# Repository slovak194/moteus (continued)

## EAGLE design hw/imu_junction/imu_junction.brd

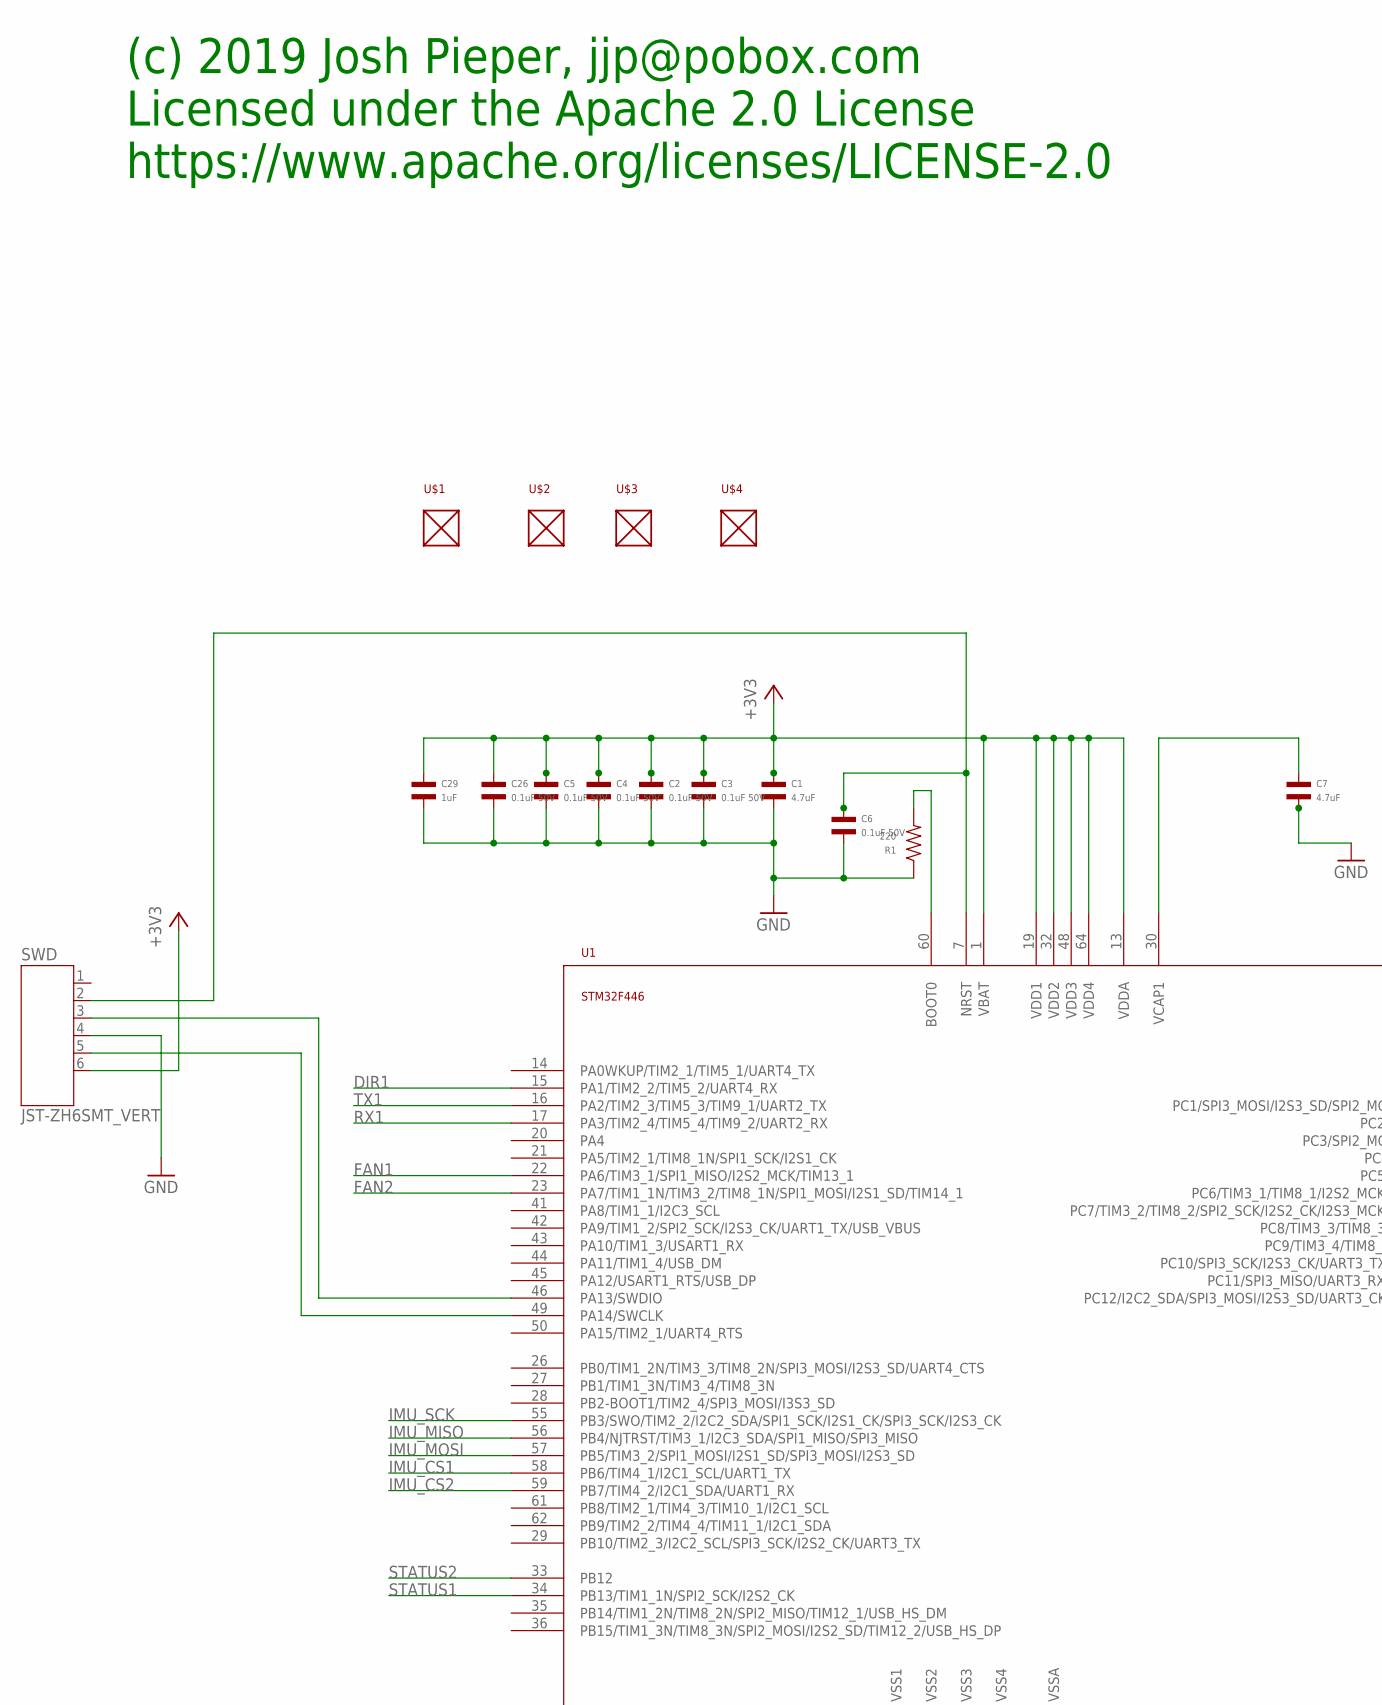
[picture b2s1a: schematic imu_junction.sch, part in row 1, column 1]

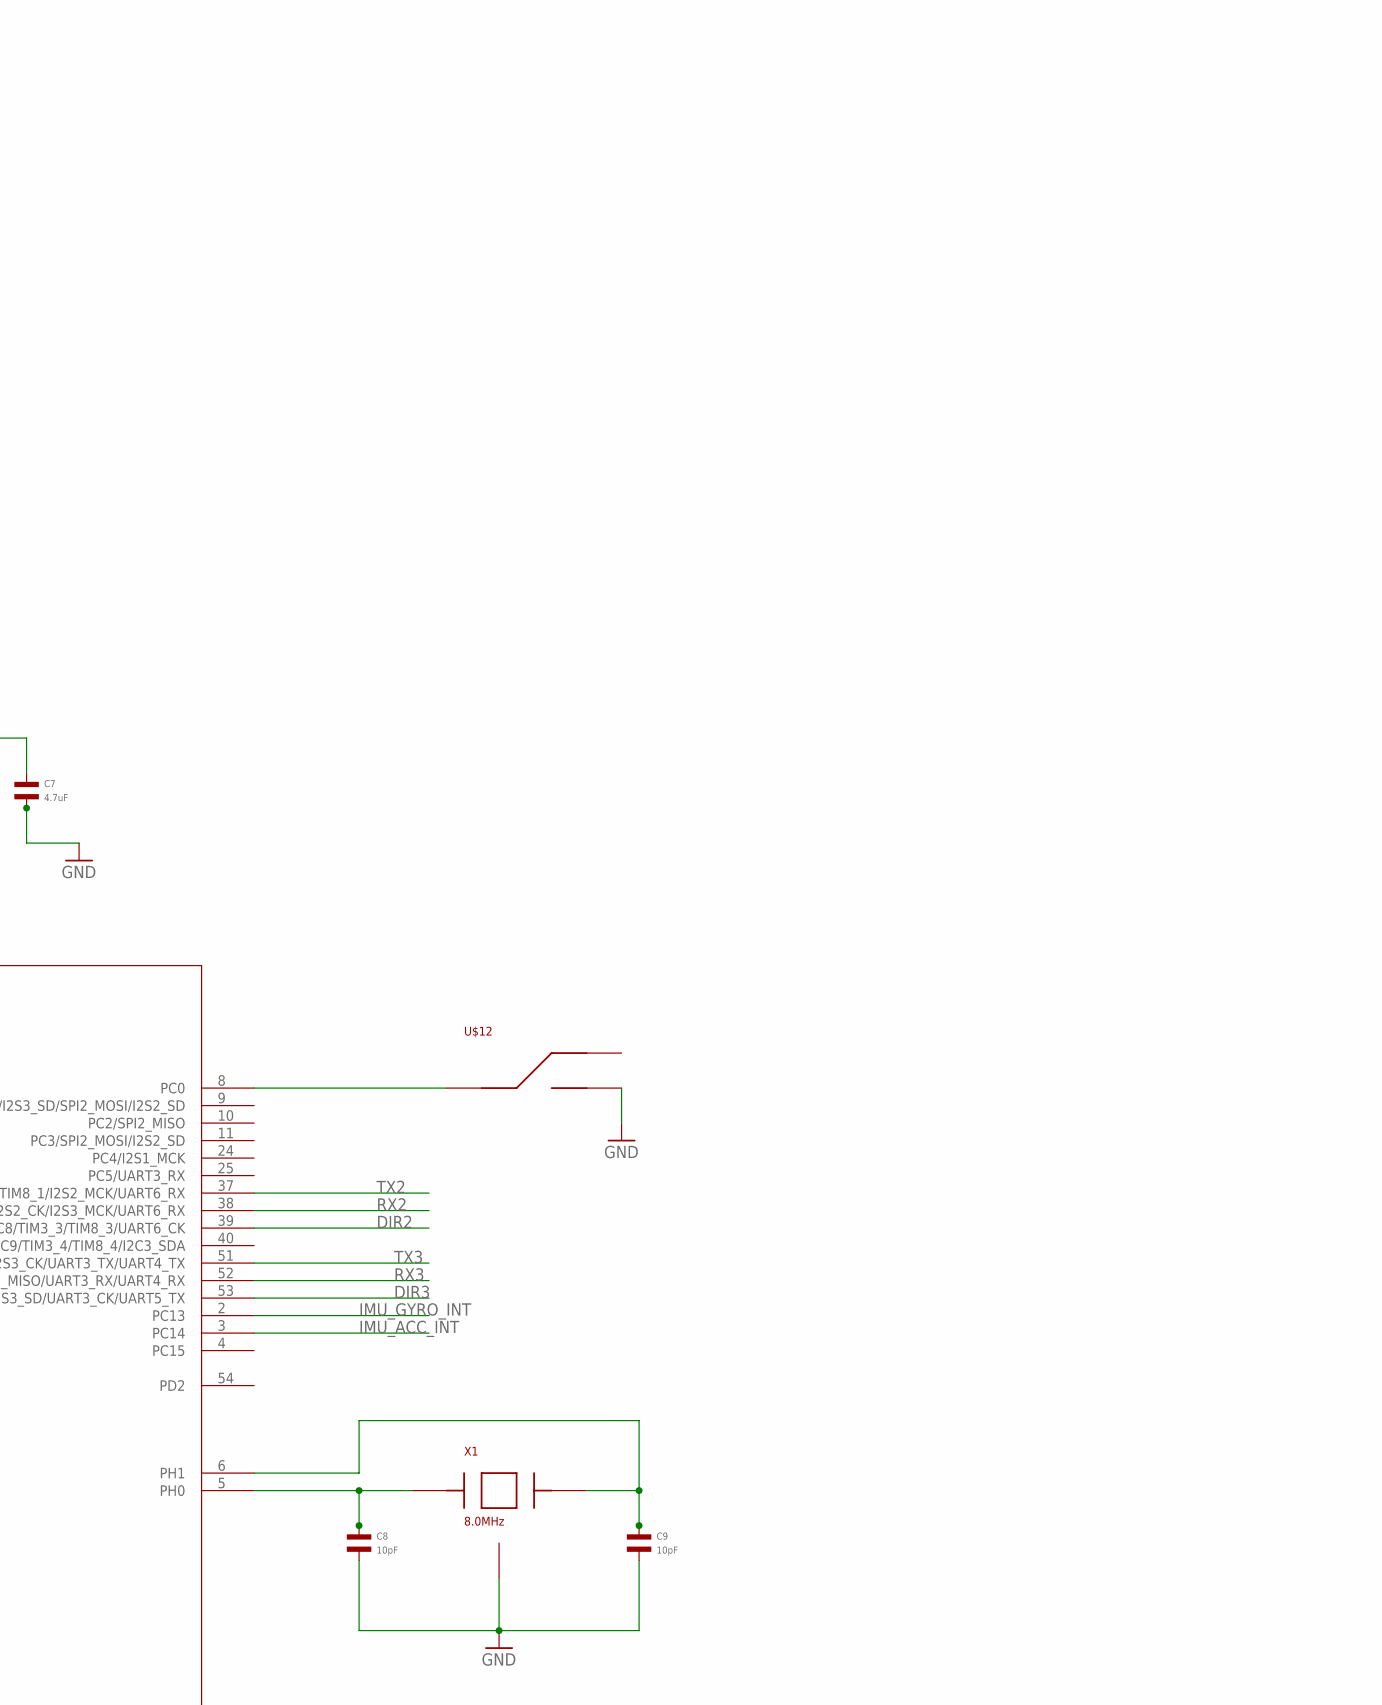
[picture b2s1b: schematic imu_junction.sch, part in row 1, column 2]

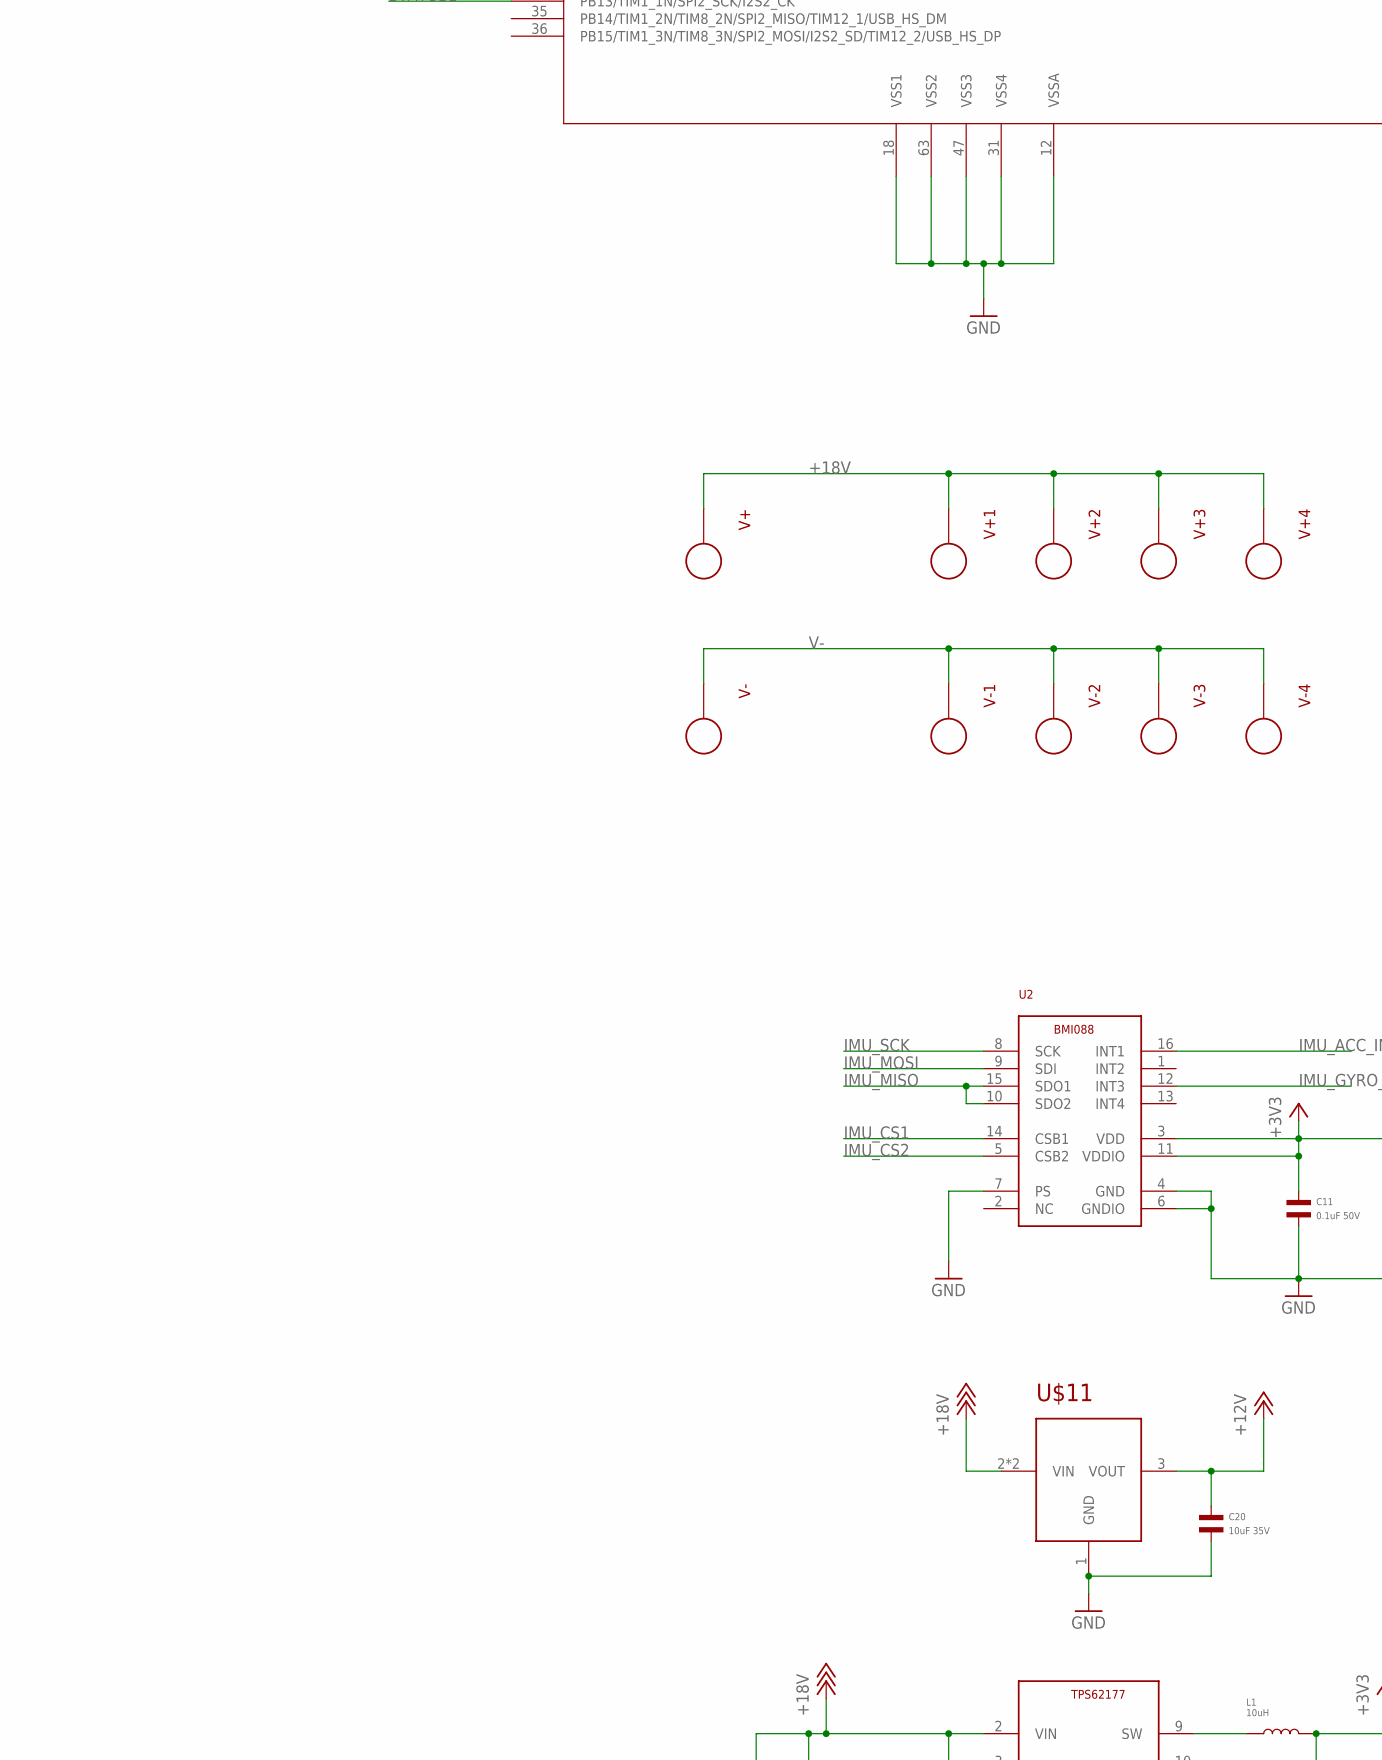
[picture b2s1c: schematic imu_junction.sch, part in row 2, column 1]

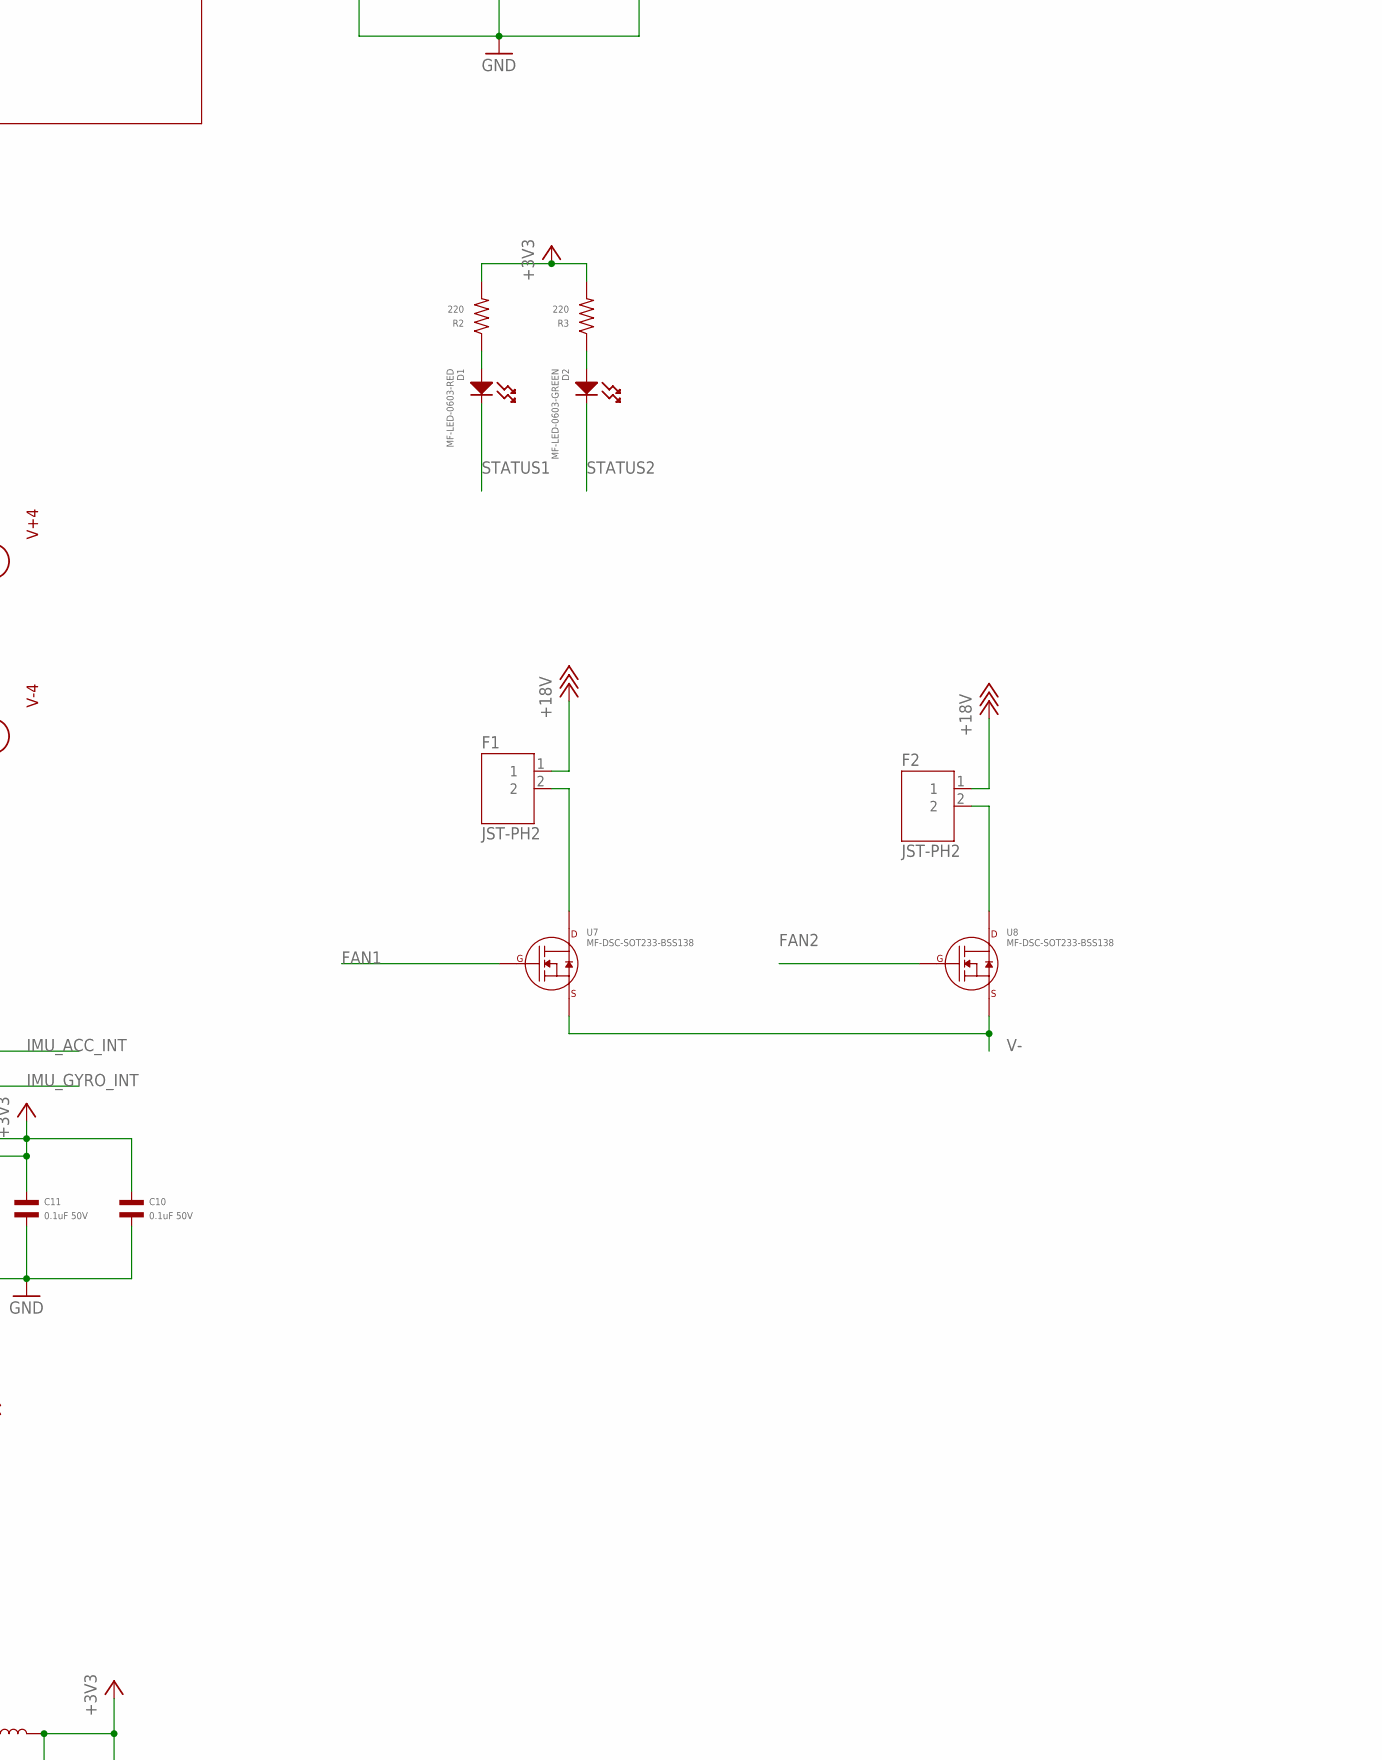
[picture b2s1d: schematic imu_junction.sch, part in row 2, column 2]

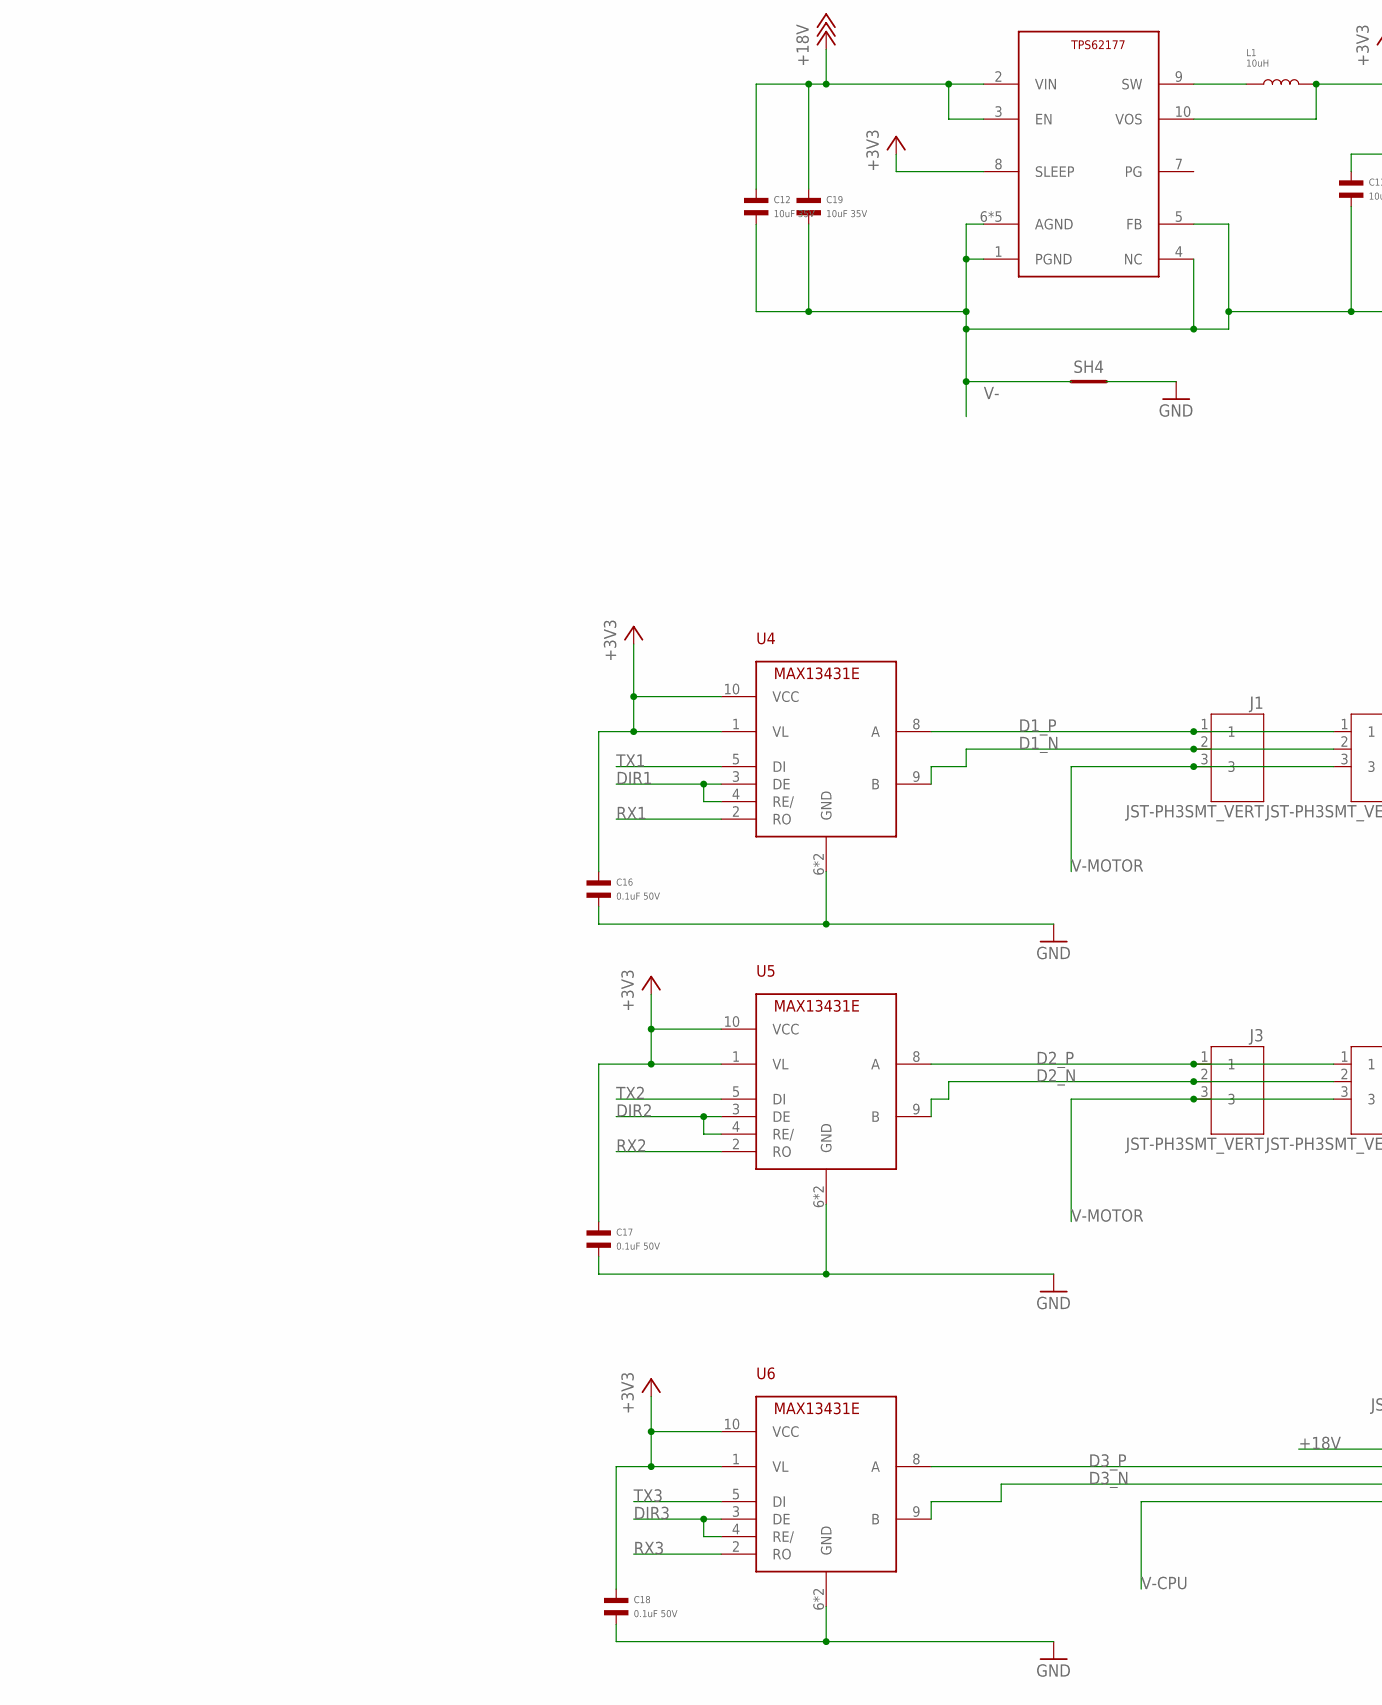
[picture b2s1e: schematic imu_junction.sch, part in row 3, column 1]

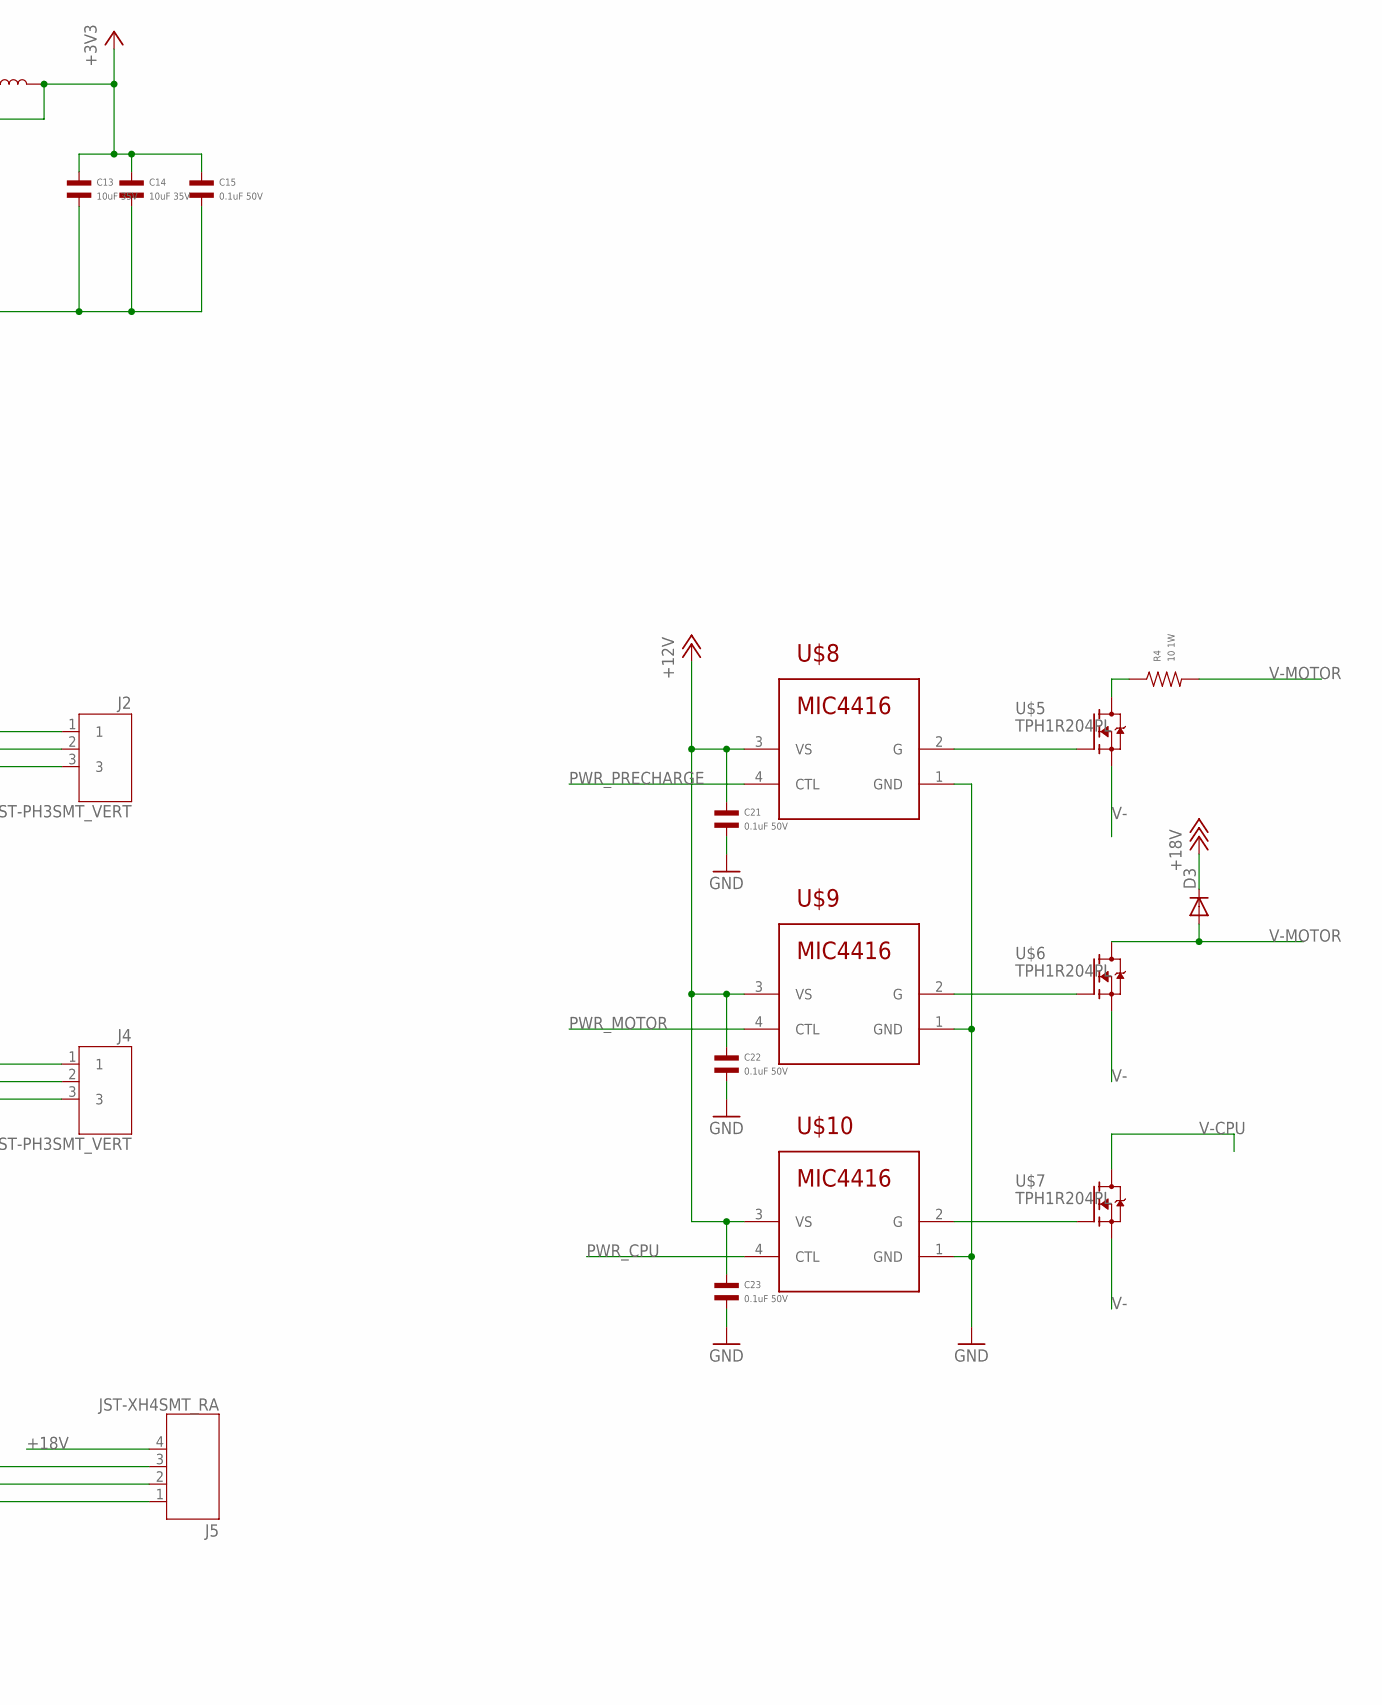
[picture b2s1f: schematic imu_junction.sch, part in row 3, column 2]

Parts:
C1, C7: 4.7uF; C0603; MPN CL10A475KA8NQNC
C2, C3, C4, C5, C6, C10, C11, C15, C16, C17, C18, C21, C22, C23, C26: 0.1uF 50V; C0402; MPN 0402B104K500CT
C8, C9: 10pF; C0603; MPN MF-CAP-0603-10pF
C12, C13, C14, C19, C20: 10uF 35V; C1206; MPN CGA5L1X7R1V106K160AC
C29: 1uF; C0402; MPN MF-CAP-0402-1uF
D1: MF-LED-0603-RED; LED0603
D2: MF-LED-0603-GREEN; LED0603
D3: DIODE-; DO-214AB
F1, F2: JST-PH2; JST_S2B-PH-SM4-TB(LF)(SN); MPN B2B-PH-SM4-TB(LF)(SN)
J1, J2, J3, J4: JST-PH3SMT_VERT; JST_B3B_PH-SM4-TB(LF)(SN); MPN B3B-PH-SM4-TB(LF)(SN)
J5: JST-XH4SMT_RA; JST_XH_SMT_RA_4; MPN S4B-XH-SM4-TB(LF)(SN)
L1: 10uH; L1210; MPN MF-IND-1210-10uH
R1, R2, R3: 220; R0402; MPN MF-RES-0402-220
R4: 10 1W; R1206; MPN HRG3216Q-10R0-D-T1
SH4: SHORTBIG; SHORT_TOP-BIG
SWD: JST-ZH6SMT_VERT; JST_B6B-ZR-SM4-TF(LF)(SN); MPN B6B-ZR-SM4-TF(LF)(SN)
U1: STM32F4R_64PIN; LQFP64; MPN STM32F446RET6
U2: BMI088LGA16; LGA16; MPN BMI088
U3: TPS62177WSON10; WSON10; MPN TPS62177DQCR
U4, U5, U6: MAX13431E; TDFN10; MPN MAX13431EETB+T
U7, U8: MF-DSC-SOT233-BSS138; SOT-23-3
U$1, U$2, U$3, U$4: MOUNTM2; M2MOUNT
U$5, U$6, U$7: TPH1R204PL; SOP_ADVANCE
U$8, U$9, U$10: MIC4416; SOT143
U$11: ZXTR2012Z; SOT89
U$12: SLIDE_SWITCHJS_SUB_SWITCH; JS_SUB_SWITCH
V+, V+1, V+2, V+3, V+4: PAD12AWG_PAD; 12AWG_PAD
V-, V-1, V-2, V-3, V-4: PAD12AWG_PAD; 12AWG_PAD
X1: 8.0MHz; ABM3B; MPN ABM3B-8.000MHZ-10-1-U-T

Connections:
+3V3: C1.P$1, C2.P$1, C3.P$1, C4.P$1, C5.P$1, C10.P$1, C11.P$1, C13.P$1, C14.P$1, C15.P$1, C16.P$1, C17.P$1, C18.P$1, C26.P$1, C29.P$1, L1.P$2, R2.P$2, R3.P$2, SWD.6, U1.1 (VBAT), U1.13 (VDDA), U1.19 (VDD1), U1.32 (VDD2), U1.48 (VDD3), U1.64 (VDD4), U2.3 (VDD), U2.11 (VDDIO), U3.8 (SLEEP), U3.10 (VOS), U4.1 (VL), U4.10 (VCC), U5.1 (VL), U5.10 (VCC), U6.1 (VL), U6.10 (VCC)
+12V: C20.P$1, C21.P$1, C22.P$1, C23.P$1, U$8.3 (VS), U$9.3 (VS), U$10.3 (VS), U$11.3 (VOUT)
+18V: C12.P$1, C19.P$1, D3.C, F1.1, F2.1, J5.4, U3.2 (VIN), U3.3 (EN), U$11.2 (VIN), U$11.PAD (VIN), V+.1, V+1.1, V+2.1, V+3.1, V+4.1
D1_N: J1.2, J2.2, U4.9 (B)
D1_P: J1.1, J2.1, U4.8 (A)
D2_N: J3.2, J4.2, U5.9 (B)
D2_P: J3.1, J4.1, U5.8 (A)
D3_N: J5.2, U6.9 (B)
D3_P: J5.3, U6.8 (A)
DIR1: U1.15 (PA1/TIM2_2/TIM5_2/UART4_RX), U4.3 (DE), U4.4 (RE/)
DIR2: U1.39 (PC8/TIM3_3/TIM8_3/UART6_CK), U5.3 (DE), U5.4 (RE/)
DIR3: U1.53 (PC12/I2C2_SDA/SPI3_MOSI/I2S3_SD/UART3_C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), U6.3 (DE), U6.4 (RE/)
FAN1: U1.22 (PA6/TIM3_1/SPI1_MISO/I2S2_MCK/TIM13_1), U7.P$1 (GATE)
FAN2: U1.23 (PA7/TIM1_1N/TIM3_2/TIM8_1N/SPI1_MOSI/I2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), U8.P$1 (GATE)
GND: C1.P$2, C2.P$2, C3.P$2, C4.P$2, C5.P$2, C6.P$2, C7.P$2, C8.P$2, C9.P$2, C10.P$2, C11.P$2, C16.P$2, C17.P$2, C18.P$2, C20.P$2, C21.P$2, C22.P$2, C23.P$2, C26.P$2, C29.P$2, R1.P$1, SH4.2, SWD.4, U1.12 (VSSA), U1.18 (VSS1), U1.31 (VSS4), U1.47 (VSS3), U1.63 (VSS2), U2.4 (GND), U2.6 (GNDIO), U2.7 (PS), U4.6 (GND), U4.PAD (GND), U5.6 (GND), U5.PAD (GND), U6.6 (GND), U6.PAD (GND), U$8.1 (GND), U$9.1 (GND), U$10.1 (GND), U$11.1 (GND), U$12.3, X1.2, X1.4
IMU_ACC_INT: U1.3 (PC14), U2.16 (INT1)
IMU_CS1: U1.58 (PB6/TIM4_1/I2C1_SCL/UART1_TX), U2.14 (CSB1)
IMU_CS2: U1.59 (PB7/TIM4_2/I2C1_SDA/UART1_RX), U2.5 (CSB2)
IMU_GYRO_INT: U1.2 (PC13), U2.12 (INT3)
IMU_MISO: U1.56 (PB4/NJTRST/TIM3_1/I2C3_SDA/SPI1_MISO/SP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), U2.10 (SDO2), U2.15 (SDO1)
IMU_MOSI: U1.57 (PB5/TIM3_2/SPI1_MOSI/I2S1_SD/SPI3_MOSI/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), U2.9 (SDI)
IMU_SCK: U1.55 (PB3/SWO/TIM2_2/I2C2_SDA/SPI1_SCK/I2S1_C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), U2.8 (SCK)
unnamed: L1.P$1, U3.9 (SW)
unnamed: U1.8 (PC0), U$12.2
unnamed: F1.2, U7.P$3 (DRAIN)
unnamed: D1.ANODE, R2.P$1
unnamed: SWD.5, U1.49 (PA14/SWCLK)
unnamed: SWD.3, U1.46 (PA13/SWDIO)
unnamed: D2.ANODE, R3.P$1
unnamed: F2.2, U8.P$3 (DRAIN)
unnamed: R4.P$1, U$5.5 (D), U$5.6 (D), U$5.7 (D), U$5.8 (D), U$5.PAD (D)
unnamed: U$6.4 (G), U$9.2 (G)
unnamed: U$5.4 (G), U$8.2 (G)
unnamed: U$7.4 (G), U$10.2 (G)
unnamed: C7.P$1, U1.30 (VCAP1)
unnamed: C6.P$1, SWD.2, U1.7 (NRST)
unnamed: R1.P$2, U1.60 (BOOT0)
unnamed: C8.P$1, U1.5 (PH0), X1.1
unnamed: C9.P$1, U1.6 (PH1), X1.3
PWR_CPU: U$10.4 (CTL)
PWR_MOTOR: U$9.4 (CTL)
PWR_PRECHARGE: U$8.4 (CTL)
RX1: U1.17 (PA3/TIM2_4/TIM5_4/TIM9_2/UART2_RX), U4.2 (RO)
RX2: U1.38 (PC7/TIM3_2/TIM8_2/SPI2_SCK/I2S2_CK/I2S3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), U5.2 (RO)
RX3: U1.52 (PC11/SPI3_MISO/UART3_RX/UART4_RX), U6.2 (RO)
STATUS1: D1.CATHODE, U1.34 (PB13/TIM1_1N/SPI2_SCK/I2S2_CK)
STATUS2: D2.CATHODE, U1.33 (PB12)
TX1: U1.16 (PA2/TIM2_3/TIM5_3/TIM9_1/UART2_TX), U4.5 (DI)
TX2: U1.37 (PC6/TIM3_1/TIM8_1/I2S2_MCK/UART6_RX), U5.5 (DI)
TX3: U1.51 (PC10/SPI3_SCK/I2S3_CK/UART3_TX/UART4_TX), U6.5 (DI)
V-: C12.P$2, C13.P$2, C14.P$2, C15.P$2, C19.P$2, SH4.1, U3.1 (PGND), U3.4 (NC), U3.5 (FB), U3.6 (AGND), U3.P0 (AGND), U3.P1 (AGND), U3.P2 (AGND), U3.P3 (AGND), U7.P$2 (SOURCE), U8.P$2 (SOURCE), U$5.1 (S), U$5.2 (S), U$5.3 (S), U$6.1 (S), U$6.2 (S), U$6.3 (S), U$7.1 (S), U$7.2 (S), U$7.3 (S), V-.1, V-1.1, V-2.1, V-3.1, V-4.1
V-CPU: J5.1, U$7.5 (D), U$7.6 (D), U$7.7 (D), U$7.8 (D), U$7.PAD (D)
V-MOTOR: D3.A, J1.3, J2.3, J3.3, J4.3, R4.P$2, U$6.5 (D), U$6.6 (D), U$6.7 (D), U$6.8 (D), U$6.PAD (D)

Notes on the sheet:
(c) 2019 Josh Pieper, jjp@pobox.com Licensed under the Apache 2.0 License https://www.apache.org/licenses/LICENSE-2.0

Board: 4 copper layers, 73 parts (0 on the bottom side), 50 nets, no tracks yet.

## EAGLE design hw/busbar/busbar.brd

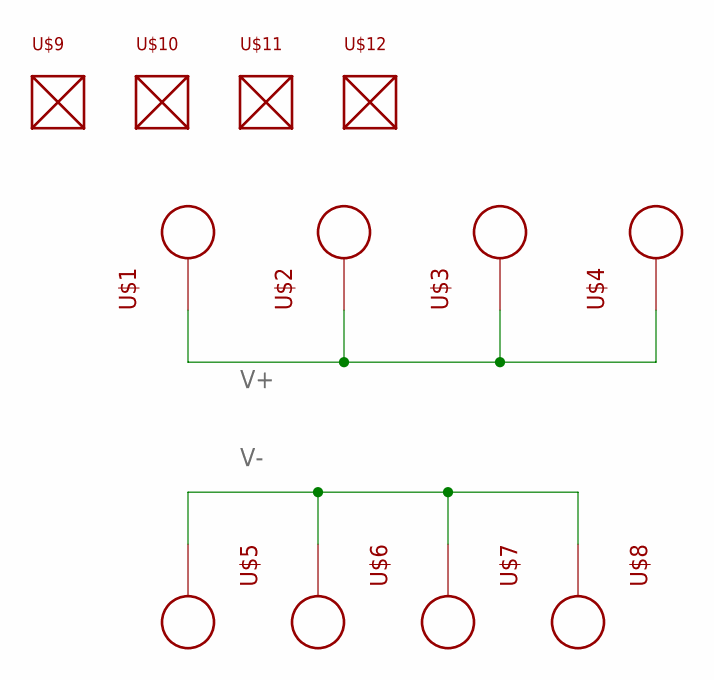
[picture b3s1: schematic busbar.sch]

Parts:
U$1, U$2, U$3, U$4, U$5, U$6, U$7, U$8: PAD12AWG_PAD; 12AWG_PAD
U$9, U$10, U$11, U$12: MOUNTM2; M2MOUNT

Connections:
V+: U$1.1, U$2.1, U$3.1, U$4.1
V-: U$5.1, U$6.1, U$7.1, U$8.1

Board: 2 copper layers, 12 parts (0 on the bottom side), 2 nets, no tracks yet.

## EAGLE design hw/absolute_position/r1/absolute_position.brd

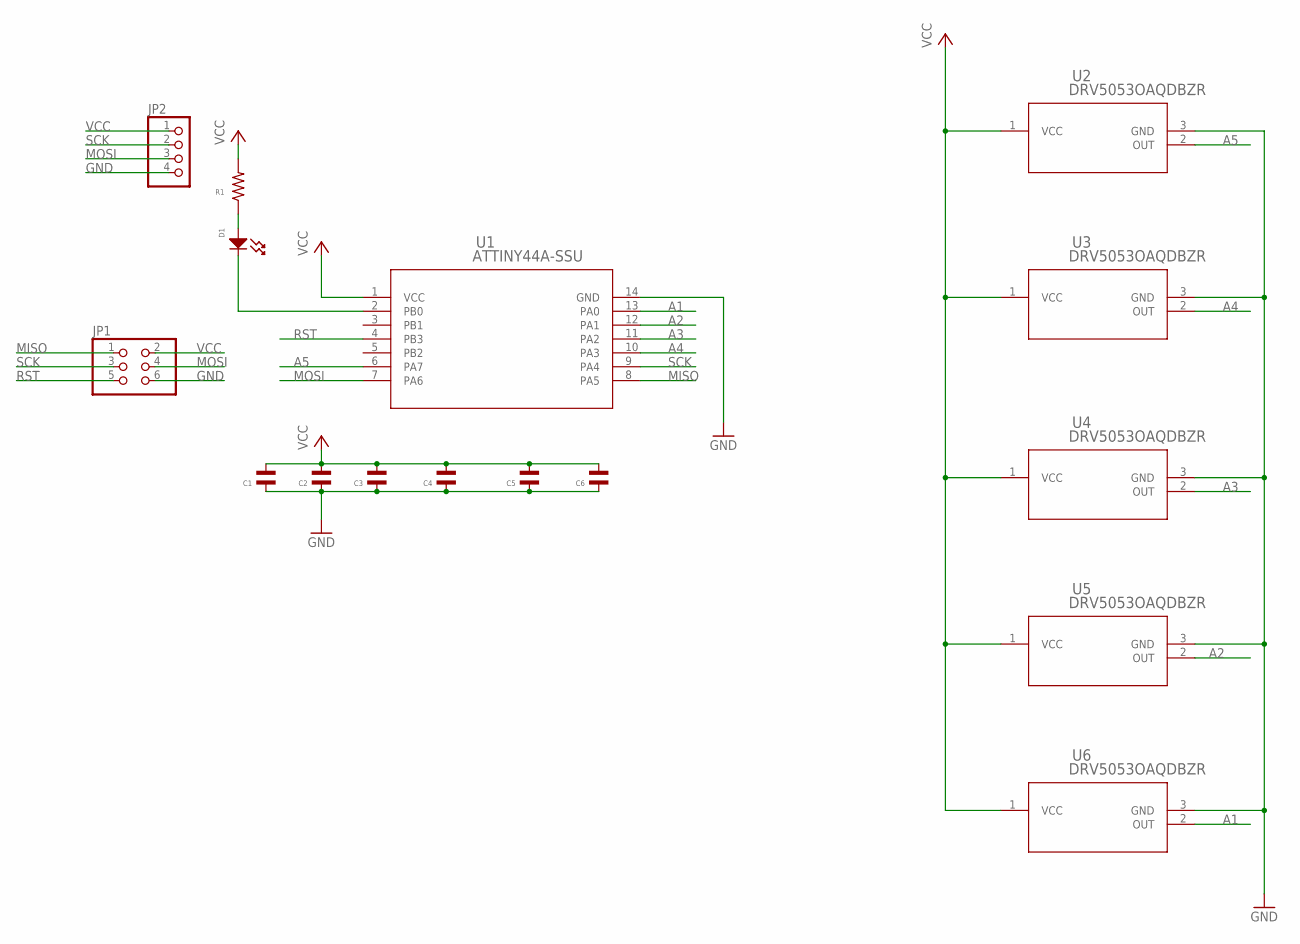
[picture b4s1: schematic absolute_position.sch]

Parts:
C1, C2, C3, C4, C5, C6: CAPACITOR_NP_0603; C0603
D1: LED_SINGLE-0603; LED0603
JP1: PINHD-2X3; 2X03
JP2: PINHD-1X4; 1X04
R1: RESISTOR_0603; R0603
U1: ATTINY44A-SSU; 14S1
U2, U3, U4, U5, U6: DRV5053OAQDBZR; DBZ3

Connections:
A1: U1.13 (PA0), U6.2 (OUT)
A2: U1.12 (PA1), U5.2 (OUT)
A3: U1.11 (PA2), U4.2 (OUT)
A4: U1.10 (PA3), U3.2 (OUT)
A5: U1.6 (PA7), U2.2 (OUT)
GND: C1.P$1, C2.P$1, C3.P$1, C4.P$1, C5.P$1, C6.P$1, JP1.6, JP2.4, U1.14 (GND), U2.3 (GND), U3.3 (GND), U4.3 (GND), U5.3 (GND), U6.3 (GND)
MISO: JP1.1, U1.8 (PA5)
MOSI: JP1.4, JP2.3, U1.7 (PA6)
unnamed: D1.ANODE, R1.P$1
unnamed: D1.CATHODE, U1.2 (PB0)
RST: JP1.5, U1.4 (PB3)
SCK: JP1.3, JP2.2, U1.9 (PA4)
VCC: C1.P$2, C2.P$2, C3.P$2, C4.P$2, C5.P$2, C6.P$2, JP1.2, JP2.1, R1.P$2, U1.1 (VCC), U2.1 (VCC), U3.1 (VCC), U4.1 (VCC), U5.1 (VCC), U6.1 (VCC)

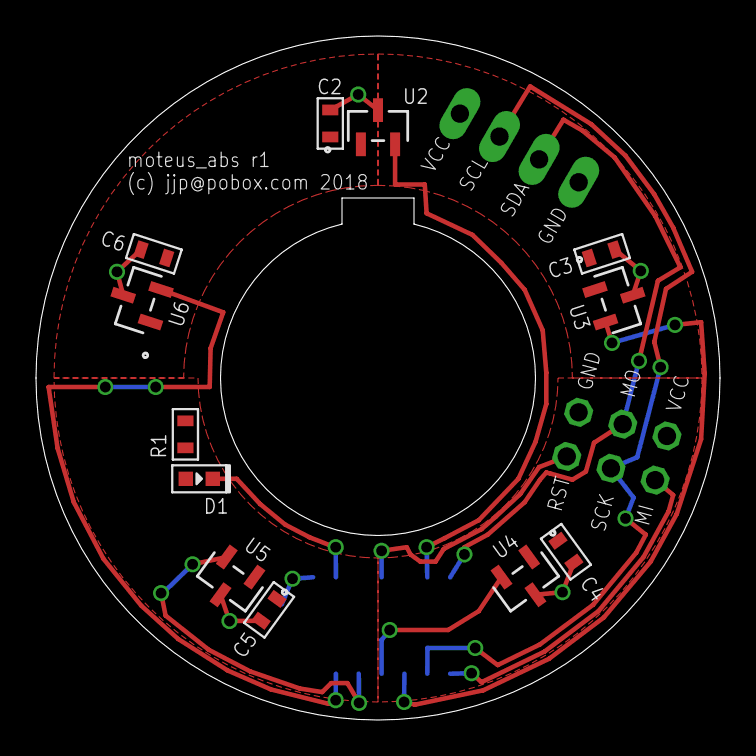
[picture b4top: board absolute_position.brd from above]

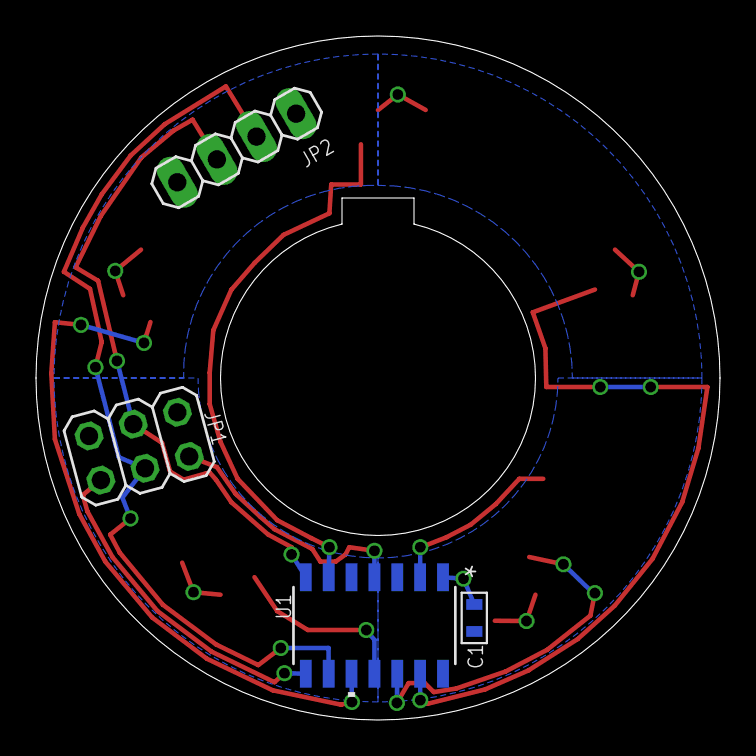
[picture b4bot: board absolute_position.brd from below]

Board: 2 copper layers, 38.0 x 38.0 mm, 16 parts (4 on the bottom side), 13 nets.

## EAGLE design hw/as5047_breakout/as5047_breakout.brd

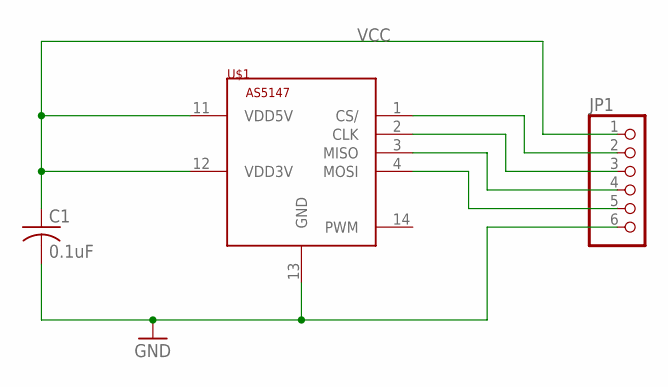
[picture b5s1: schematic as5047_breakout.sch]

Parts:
C1: 0.1uF; C0603
JP1: PINHD-1X6; 1X06
U$1: AS5147; TSSOP14; MPN AS5047D-ATSM

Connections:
GND: C1.2, JP1.6, U$1.13 (GND)
unnamed: JP1.5, U$1.4 (MOSI)
unnamed: JP1.4, U$1.3 (MISO)
unnamed: JP1.3, U$1.2 (CLK)
unnamed: JP1.2, U$1.1 (CS/)
VCC: C1.1, JP1.1, U$1.11 (VDD5V), U$1.12 (VDD3V)

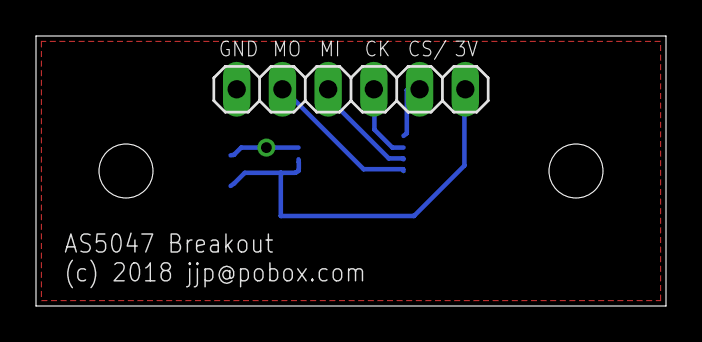
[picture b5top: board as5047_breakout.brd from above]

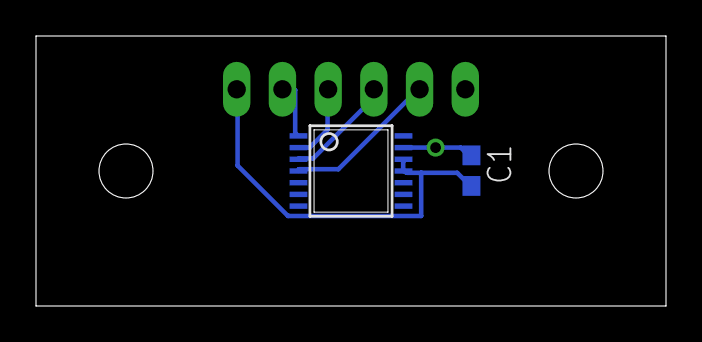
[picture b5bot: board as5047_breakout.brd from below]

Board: 2 copper layers, 35.0 x 15.0 mm, 3 parts (2 on the bottom side), 6 nets.

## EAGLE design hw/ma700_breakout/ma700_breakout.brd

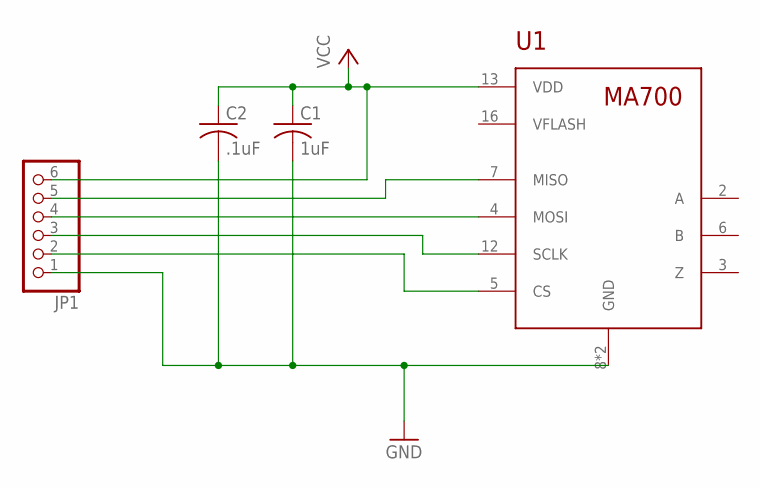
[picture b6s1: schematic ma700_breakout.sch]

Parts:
C1: 1uF; C0603
C2: .1uF; C0603
JP1: PINHD-1X6; 1X06
U1: MA700; QFN-16

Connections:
GND: C1.2, C2.2, JP1.1, U1.8 (GND), U1.PAD (GND)
unnamed: JP1.2, U1.5 (CS)
unnamed: JP1.3, U1.12 (SCLK)
unnamed: JP1.4, U1.4 (MOSI)
unnamed: JP1.5, U1.7 (MISO)
VCC: C1.1, C2.1, JP1.6, U1.13 (VDD)
